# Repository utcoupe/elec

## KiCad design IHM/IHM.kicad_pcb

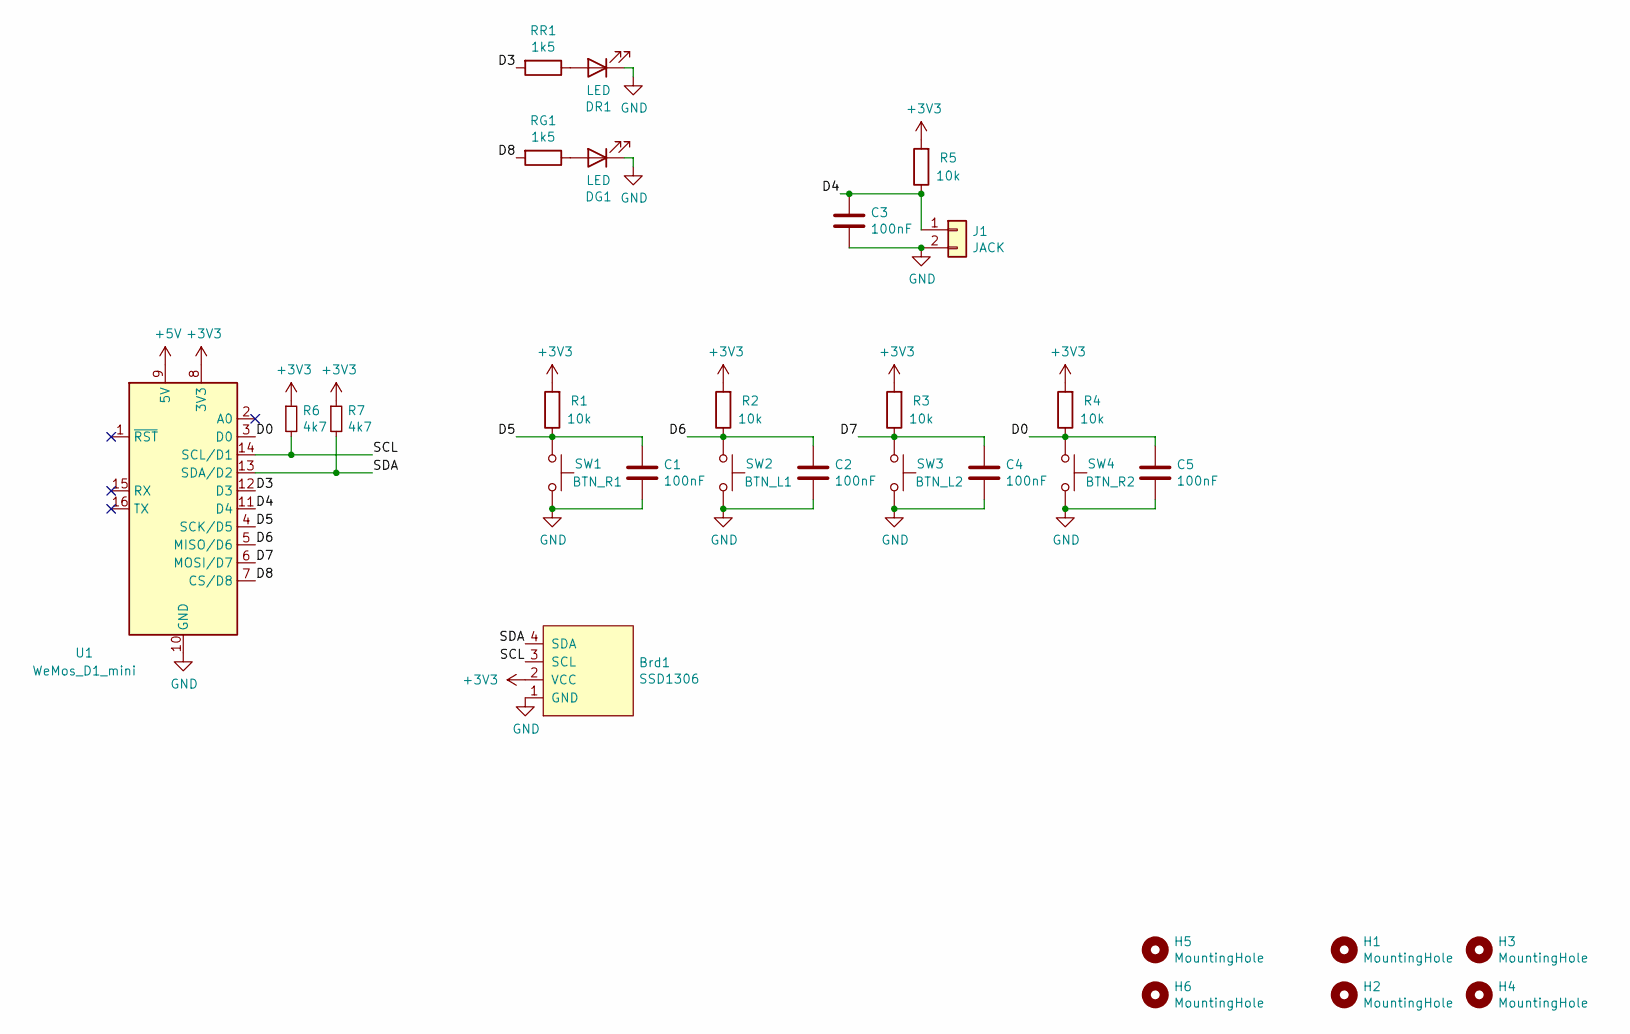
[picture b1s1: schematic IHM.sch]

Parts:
Brd1: SSD1306; 128x64OLED
C1, C2, C3, C4, C5: 100nF; C_0603_1608Metric; LCSC C14663
DG1: LED; LED_D3.0mm
DR1: LED; LED_D3.0mm
H1, H2, H3, H4: MountingHole; MountingHole_3.2mm_M3
H5, H6: MountingHole; MountingHole_2.2mm_M2
J1: JACK; PhoenixContact_MC_1,5_2-G-3.5_1x02_P3.50mm_Horizontal
R1, R2, R3, R4, R5: 10k; R_0603_1608Metric; LCSC C25804
R6, R7: 4k7; R_0603_1608Metric; LCSC C23162
RG1: 1k5; R_0603_1608Metric; LCSC C22843
RR1: 1k5; R_0603_1608Metric; LCSC C22843
SW1: BTN_R1; SW_PUSH_6mm_H4.3mm
SW2: BTN_L1; SW_PUSH_6mm_H4.3mm
SW3: BTN_L2; SW_PUSH_6mm_H4.3mm
SW4: BTN_R2; SW_PUSH_6mm_H4.3mm
U1: WeMos_D1_mini; WEMOS_D1_mini_light

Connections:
+3V3: Brd1.2 (VCC), R1.2, R2.2, R3.2, R4.2, R5.2, R6.1, R7.1, U1.8 (3V3)
+5V: U1.9 (5V)
/D0: C5.1, R4.1, SW4.1, U1.3 (D0)
/D3: RR1.2, U1.12 (D3)
/D4: C3.1, J1.1, R5.1, U1.11 (D4)
/D5: C1.1, R1.1, SW1.1, U1.4 (SCK/D5)
/D6: C2.1, R2.1, SW2.1, U1.5 (MISO/D6)
/D7: C4.1, R3.1, SW3.1, U1.6 (MOSI/D7)
/D8: RG1.2, U1.7 (CS/D8)
/SCL: Brd1.3 (SCL), R6.2, U1.14 (SCL/D1)
/SDA: Brd1.4 (SDA), R7.2, U1.13 (SDA/D2)
GND: Brd1.1 (GND), C1.2, C2.2, C3.2, C4.2, C5.2, DG1.1 (K), DR1.1 (K), J1.2, SW1.2, SW2.2, SW3.2, SW4.2, U1.10 (GND)
unnamed: DG1.2 (A), RG1.1
unnamed: DR1.2 (A), RR1.1

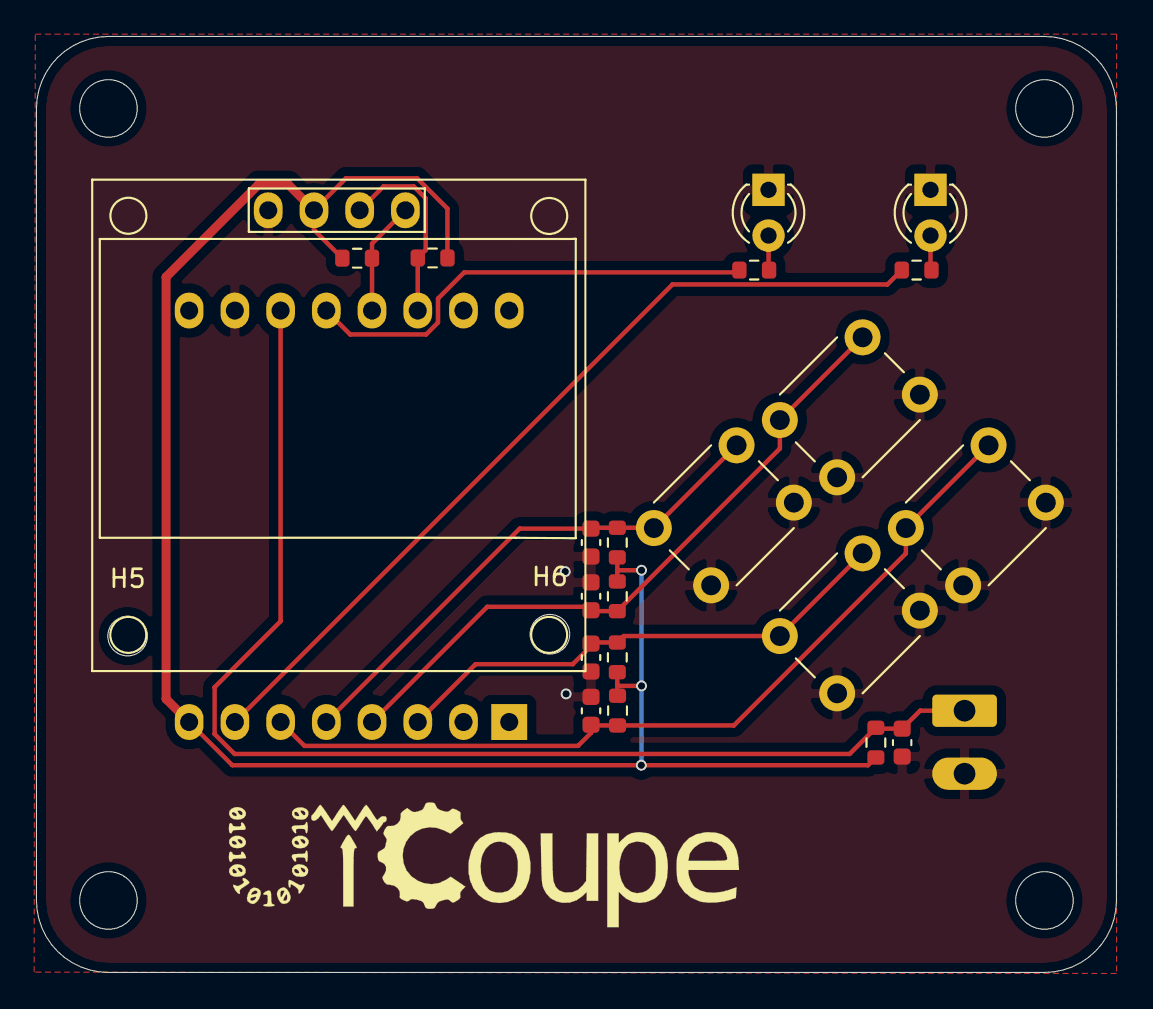
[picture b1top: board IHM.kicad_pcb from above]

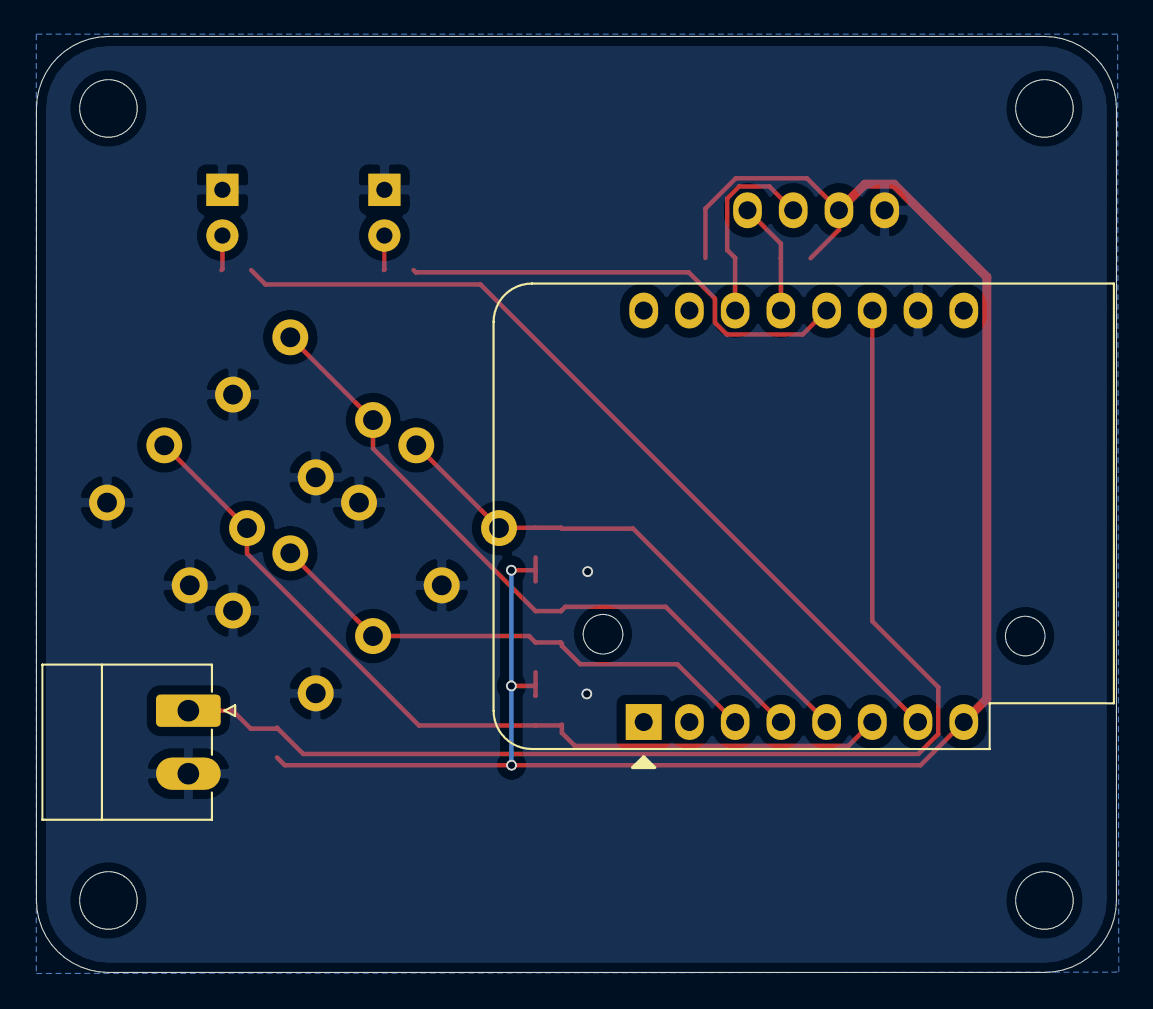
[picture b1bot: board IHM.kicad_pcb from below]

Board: 2 copper layers, 60.0 x 52.0 mm, 29 parts (2 on the bottom side), 13 nets.

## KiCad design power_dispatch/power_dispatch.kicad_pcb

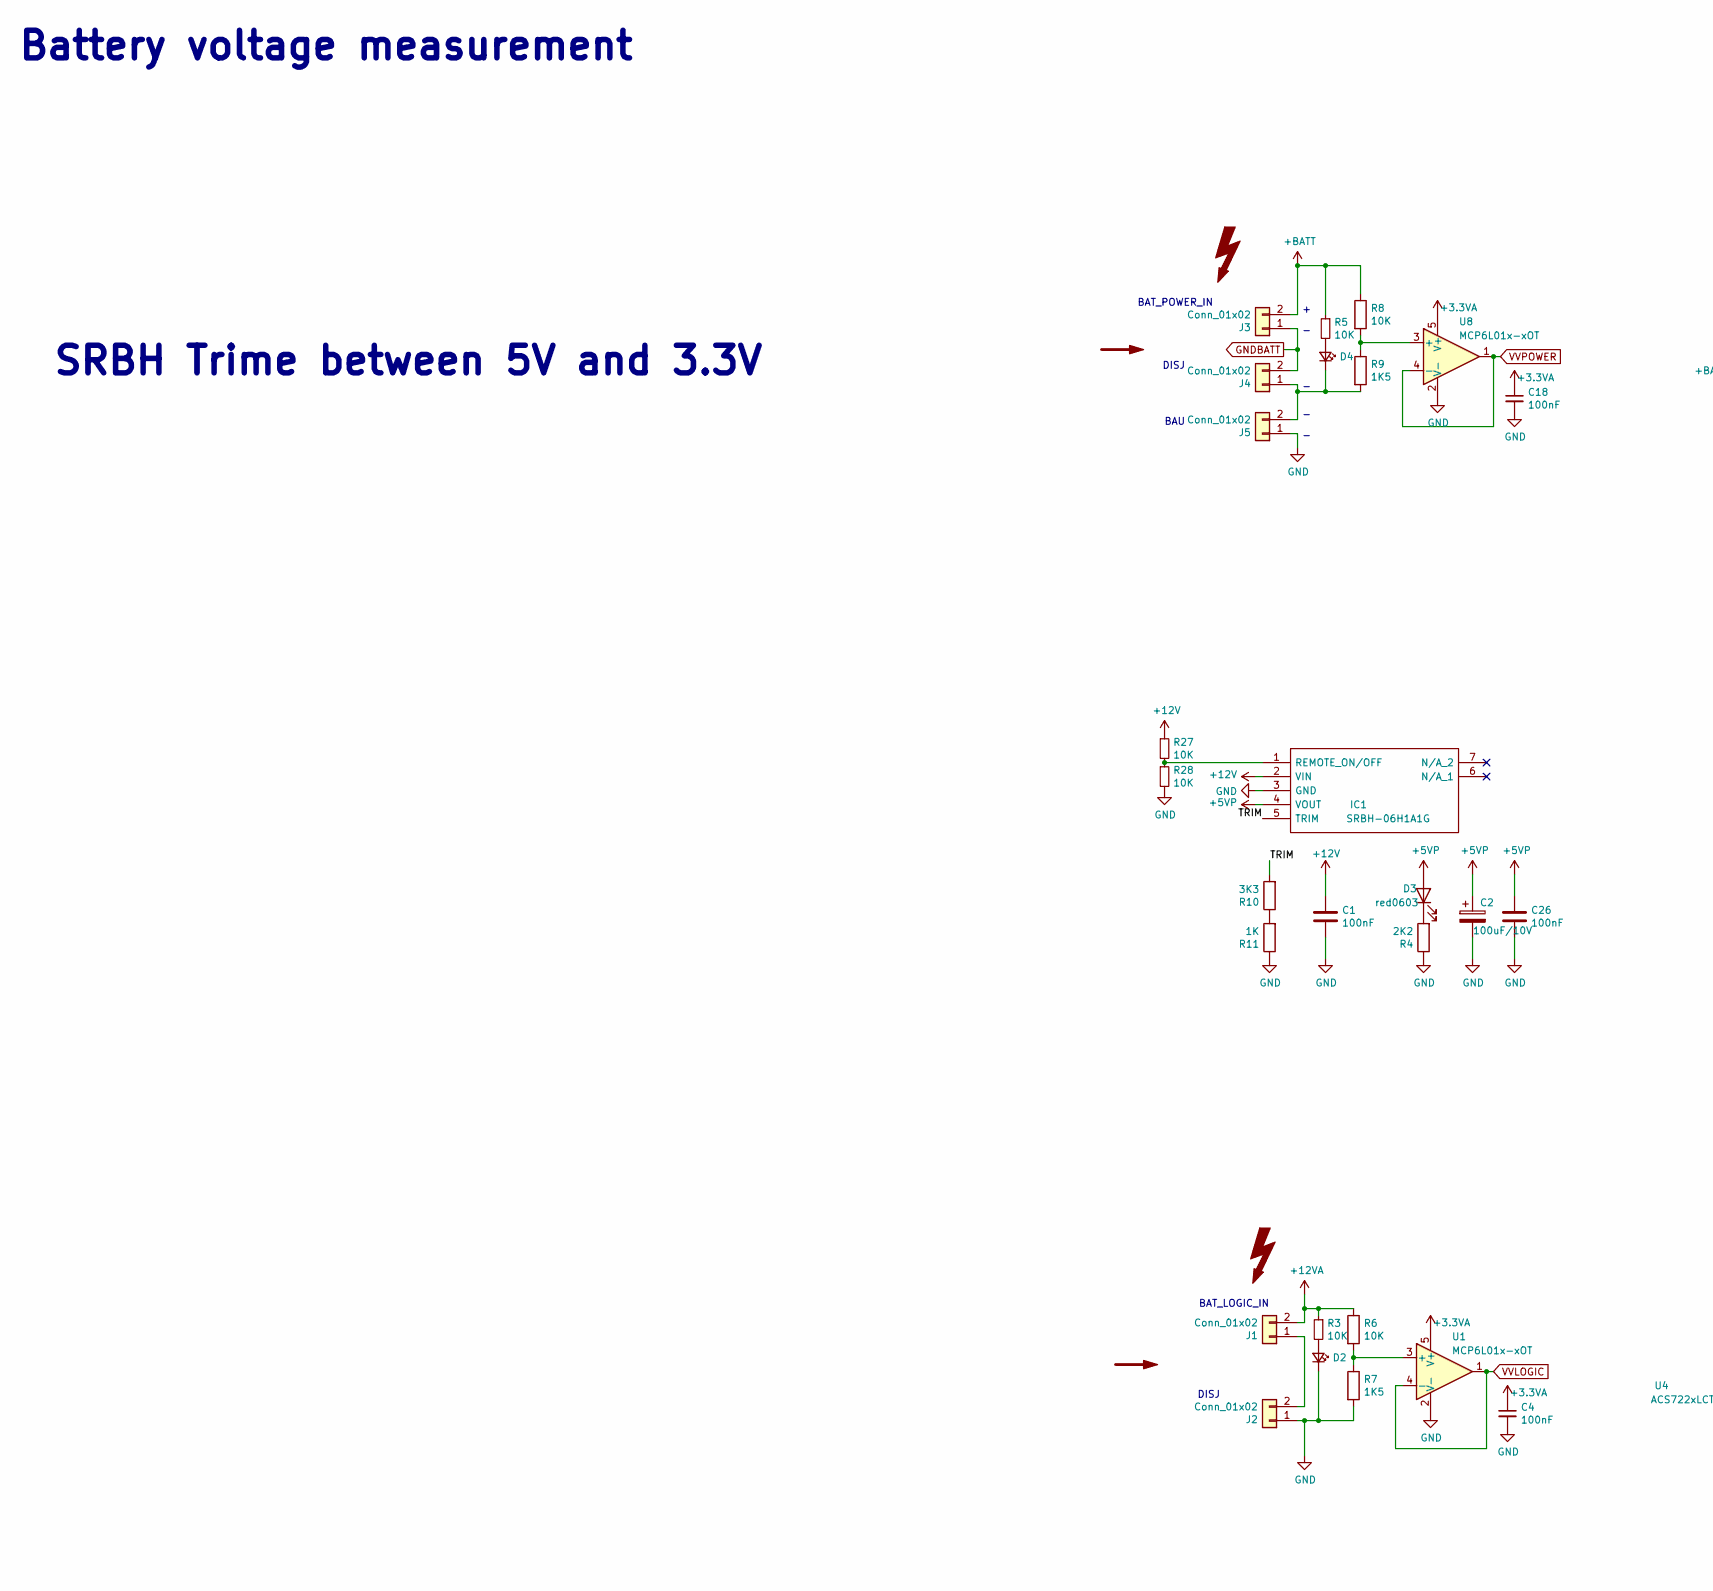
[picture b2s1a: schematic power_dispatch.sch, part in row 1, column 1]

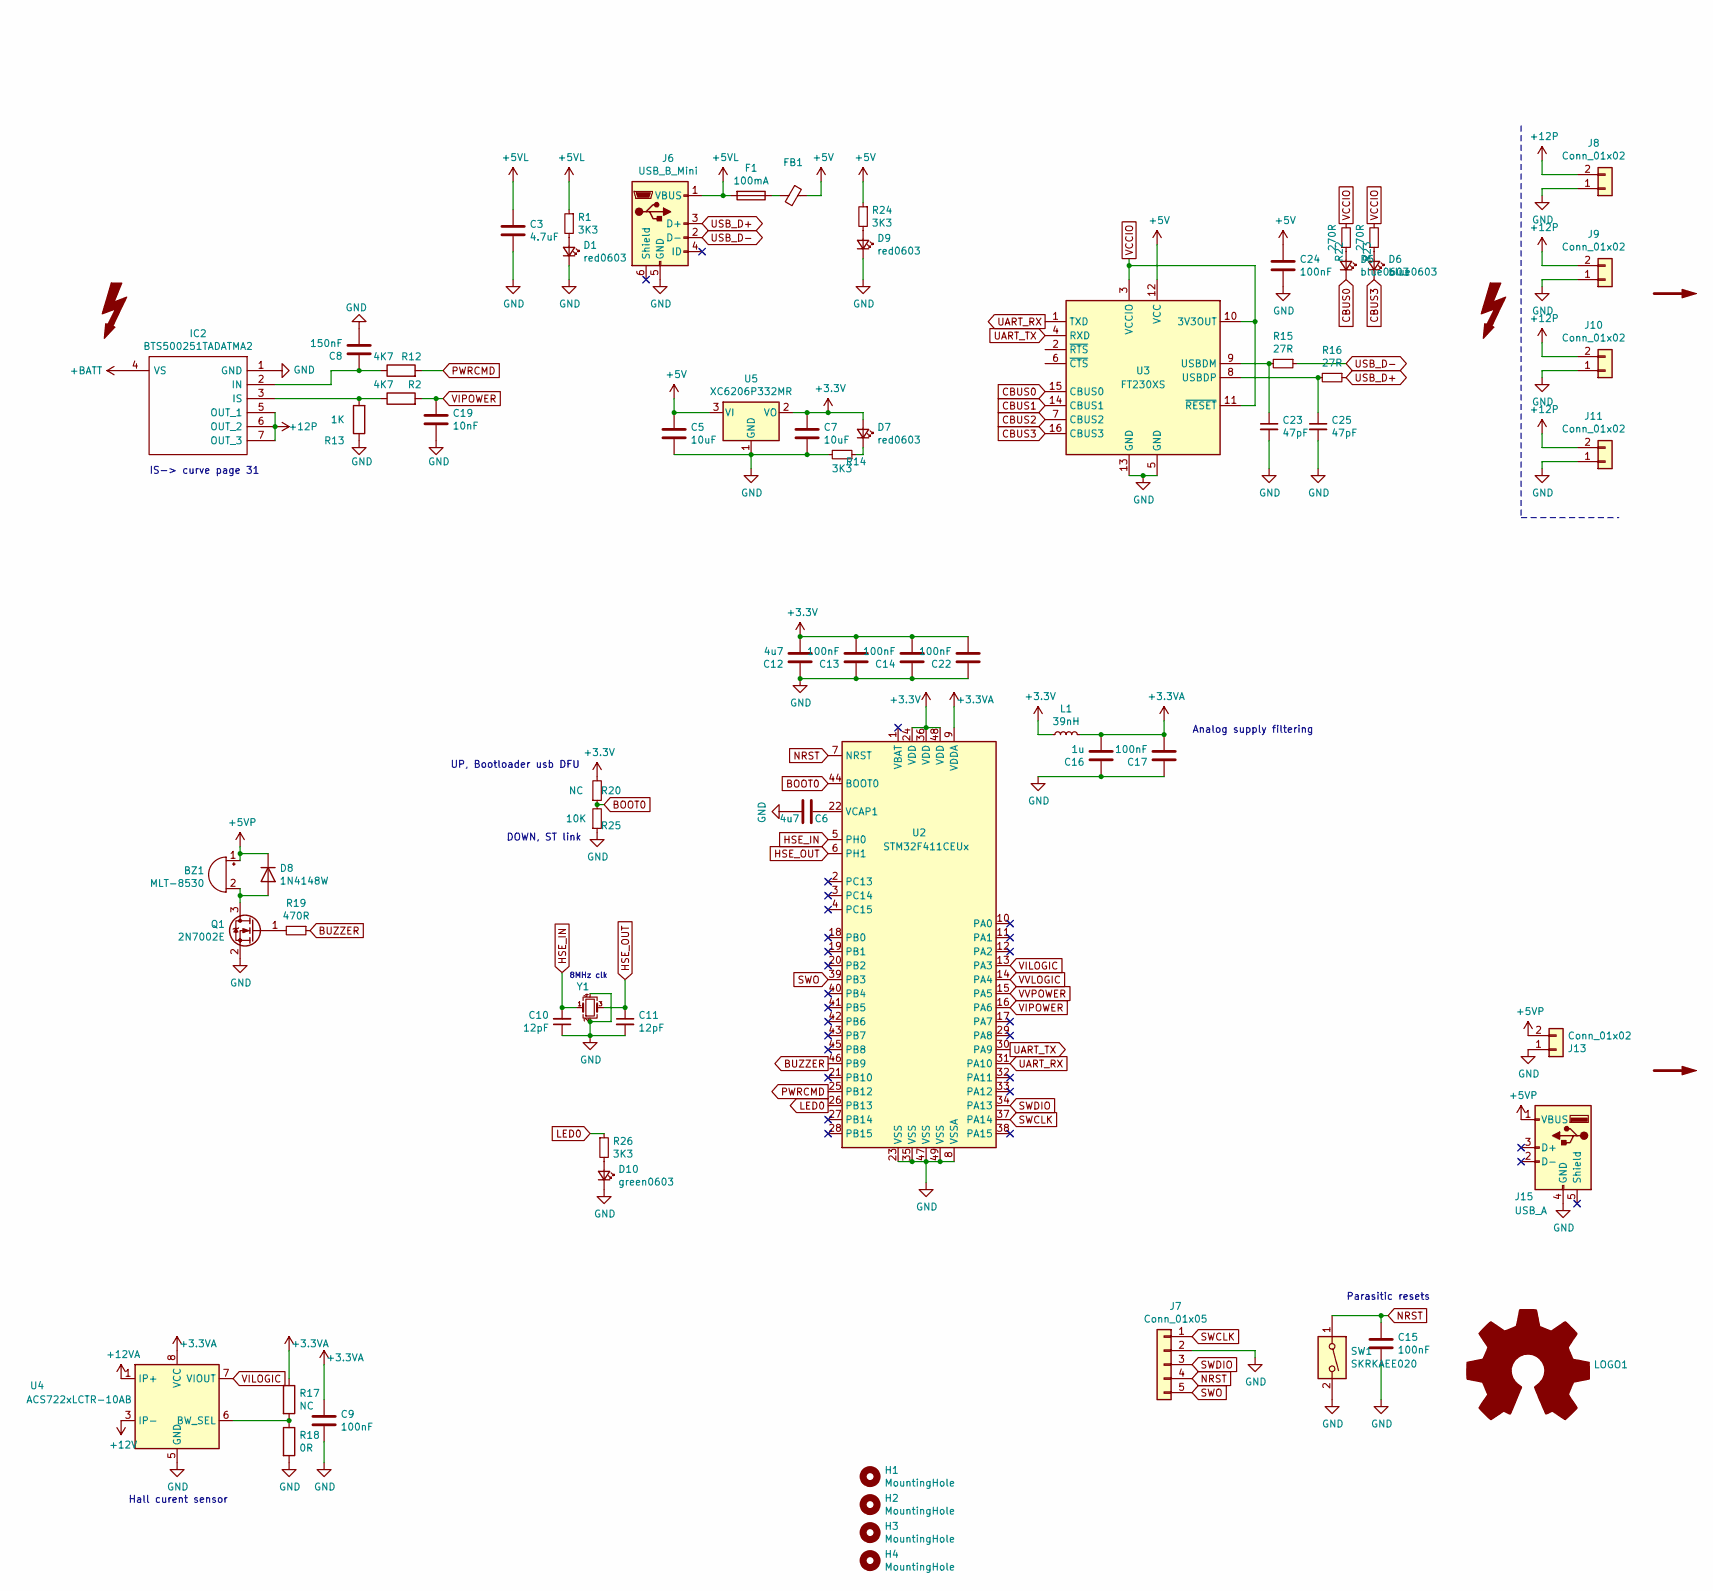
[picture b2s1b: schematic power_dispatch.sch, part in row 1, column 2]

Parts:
BZ1: MLT-8530; MagneticBuzzer_Kobitone_254-EMB84Q-RO
C1, C4, C9, C13, C14, C15, C17, C18, C22, C24, C26: 100nF; C_0603_1608Metric
C2: 100uF/10V; CP_Elec_5x5.4
C3: 4.7uF; C_0603_1608Metric
C5, C7: 10uF; C_0603_1608Metric
C6, C12: 4u7; C_0603_1608Metric
C8: 150nF; C_0603_1608Metric
C10, C11: 12pF; C_0603_1608Metric
C16: 1u; C_0603_1608Metric
C19: 10nF; C_0603_1608Metric
C23, C25: 47pF; C_0603_1608Metric
D1, D2, D3, D4, D7, D9: red0603; LED_0603_1608Metric
D5, D6: blue0603; LED_0603_1608Metric
D8: 1N4148W; D_SOD-123
D10: green0603; LED_0603_1608Metric
F1: 100mA; Fuse_0603_1608Metric
FB1: 100 @ 100MHz; L_0805_2012Metric
H1, H2, H3, H4: MountingHole; MountingHole_2.2mm_M2
IC1: SRBH-06H1A1G; SRBH06H1A1G; Manufacturer_Part_Number SRBH-06H1A1G; Mouser Part Number 784-SRBH-06H1A1G
IC2: BTS500251TADATMA2; IPB180N03S4L01; Manufacturer_Part_Number BTS500251TADATMA2; Mouser Part Number 726-BTS500251TADATM2
J1, J2, J3, J4, J5, J8, J9, J10, J11: Conn_01x02; PhoenixContact_MSTBA_2,5_2-G_1x02_P5.00mm_Horizontal
J6: USB_B_Mini; USB_Mini-B_Wuerth_65100516121_Horizontal
J7: Conn_01x05; PinHeader_1x05_P2.54mm_Vertical
J13: Conn_01x02; PhoenixContact_MC_1,5_2-G-3.5_1x02_P3.50mm_Horizontal
J15: USB_A; USB_A_Molex_67643_Horizontal
L1: 39nH; L_0603_1608Metric
LOGO1: Logo_Open_Hardware_Large; OSHW-Logo_7.5x8mm_SilkScreen
Q1: 2N7002E; SOT-23
R1, R10, R14, R24, R26: 3K3; R_0603_1608Metric
R2, R12: 4K7; R_0603_1608Metric
R3, R5, R6, R8, R25, R27, R28: 10K; R_0603_1608Metric
R4: 2K2; R_0603_1608Metric
R7, R9: 1K5; R_0603_1608Metric
R11, R13: 1K; R_0603_1608Metric
R15, R16: 27R; C_0603_1608Metric
R17, R20: NC; R_0603_1608Metric
R18: 0R; R_0603_1608Metric
R19: 470R; C_0603_1608Metric
R22, R23: 270R; R_0603_1608Metric
SW1: SKRKAEE020; SW_Push_SPST_NO_Alps_SKRK
U1, U8: MCP6L01x-xOT; SOT-23-5
U2: STM32F411CEUx; QFN-48-1EP_7x7mm_P0.5mm_EP5.6x5.6mm_ThermalVias
U3: FT230XS; SSOP-16_3.9x4.9mm_P0.635mm
U4: ACS722xLCTR-10AB; SOIC-8_3.9x4.9mm_P1.27mm
U5: XC6206P332MR; SOT-23
Y1: 1C208000BC0K 8MHz; Crystal_SMD_3225-4Pin_3.2x2.5mm

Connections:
+3.3VA: C4.1, C9.1, C16.2, C17.2, C18.1, L1.2, R17.1, U1.5 (V+), U2.9 (VDDA), U4.8 (VCC), U8.5 (V+)
+3V3: C7.1, C12.2, C13.2, C14.2, C22.2, D7.2 (A), L1.1, R20.2, U2.24 (VDD), U2.36 (VDD), U2.48 (VDD), U5.2 (VO)
+5V: C5.1, C24.1, FB1.1, R24.1, U3.12 (VCC), U5.3 (VI)
+5VL: C3.1, F1.2, J6.1 (VBUS), R1.1
+5VP: BZ1.1 (-), C2.1, C26.1, D3.2 (A), D8.1 (K), IC1.4 (VOUT), J13.2, J15.1 (VBUS)
+12P: IC2.5 (OUT_1), IC2.6 (OUT_2), IC2.7 (OUT_3), J8.2, J9.2, J10.2, J11.2
+12V: C1.1, IC1.2 (VIN), R27.1, U4.3 (IP-), U4.4 (IP-)
+12VA: J1.2, R3.1, R6.1, U4.1 (IP+), U4.2 (IP+)
+BATT: IC2.4 (VS), J3.2, R5.1, R8.1
/TRIM: IC1.5 (TRIM), R10.2
BOOT0: R20.1, R25.2, U2.44 (BOOT0)
BUZZER: R19.1, U2.46 (PB9)
CBUS0: D5.1 (K), U3.15 (CBUS0)
CBUS1: U3.14 (CBUS1)
CBUS2: U3.7 (CBUS2)
CBUS3: D6.1 (K), U3.16 (CBUS3)
GND: C1.2, C2.2, C3.2, C4.2, C5.2, C6.2, C7.2, C8.2, C9.2, C10.1, C11.2, C12.1, C13.1, C14.1, C15.2, C16.1, C17.1, C18.2, C19.2, C22.1, C23.2, C24.2, C25.2, C26.2, D1.1 (K), D2.1 (K), D9.1 (K), D10.1 (K), IC1.3 (GND), IC2.1 (GND), J2.1, J5.1, J6.5 (GND), J7.2, J8.1, J9.1, J10.1, J11.1, J13.1, J15.4 (GND), Q1.2 (S), R4.1, R7.2, R11.1, R13.1, R14.2, R18.2, R25.1, R28.2, SW1.2, U1.2 (V-), U2.8 (VSSA), U2.23 (VSS), U2.35 (VSS), U2.47 (VSS), U2.49 (VSS), U3.5 (GND), U3.13 (GND), U4.5 (GND), U5.1 (GND), U8.2 (V-), Y1.2, Y1.4
GNDBATT: J3.1, J4.2
HSE_IN: C10.2, U2.5 (PH0), Y1.1
HSE_OUT: C11.1, U2.6 (PH1), Y1.3
LED0: R26.1, U2.26 (PB13)
NRST: C15.1, J7.4, SW1.1, U2.7 (NRST)
unnamed: BZ1.2 (+), D8.2 (A), Q1.3 (D)
unnamed: C6.1, U2.22 (VCAP1)
unnamed: C8.1, IC2.2 (IN), R12.1
unnamed: C23.1, R15.2, U3.9 (USBDM)
unnamed: C25.1, R16.2, U3.8 (USBDP)
unnamed: D1.2 (A), R1.2
unnamed: D2.2 (A), R3.2
unnamed: D3.1 (K), R4.2
unnamed: D4.1 (K), J4.1, J5.2, R9.2
unnamed: D4.2 (A), R5.2
unnamed: D5.2 (A), R22.1
unnamed: D6.2 (A), R23.1
unnamed: D7.1 (K), R14.1
unnamed: D9.2 (A), R24.2
unnamed: D10.2 (A), R26.2
unnamed: F1.1, FB1.2
unnamed: IC1.1 (REMOTE_ON/OFF), R27.2, R28.1
unnamed: IC2.3 (IS), R2.1, R13.2
unnamed: J1.1, J2.2
unnamed: Q1.1 (G), R19.2
unnamed: R6.2, R7.1, U1.3 (+)
unnamed: R8.2, R9.1, U8.3 (+)
unnamed: R10.1, R11.2
unnamed: R17.2, R18.1, U4.6 (BW_SEL)
PWRCMD: R12.2, U2.25 (PB12)
SWCLK: J7.1, U2.37 (PA14)
SWDIO: J7.3, U2.34 (PA13)
SWO: J7.5, U2.39 (PB3)
UART_RX: U2.31 (PA10), U3.1 (TXD)
UART_TX: U2.30 (PA9), U3.4 (RXD)
USB_D+: J6.3 (D+), R16.1
USB_D-: J6.2 (D-), R15.1
VCCIO: R22.2, R23.2, U3.3 (VCCIO), U3.10 (3V3OUT), U3.11 (~RESET)
VILOGIC: U2.13 (PA3), U4.7 (VIOUT)
VIPOWER: C19.1, R2.2, U2.16 (PA6)
VVLOGIC: U1.1, U1.4 (-), U2.14 (PA4)
VVPOWER: U2.15 (PA5), U8.1, U8.4 (-)

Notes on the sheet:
BAT_POWER_IN
DISJ
BAU
UP, Bootloader usb DFU
DOWN, ST link
Parasitic resets
Analog supply filtering
8MHz clk
BAT_LOGIC_IN
Hall curent sensor
Battery voltage measurement
SRBH Trime between 5V and 3.3V
IS-> curve page 31

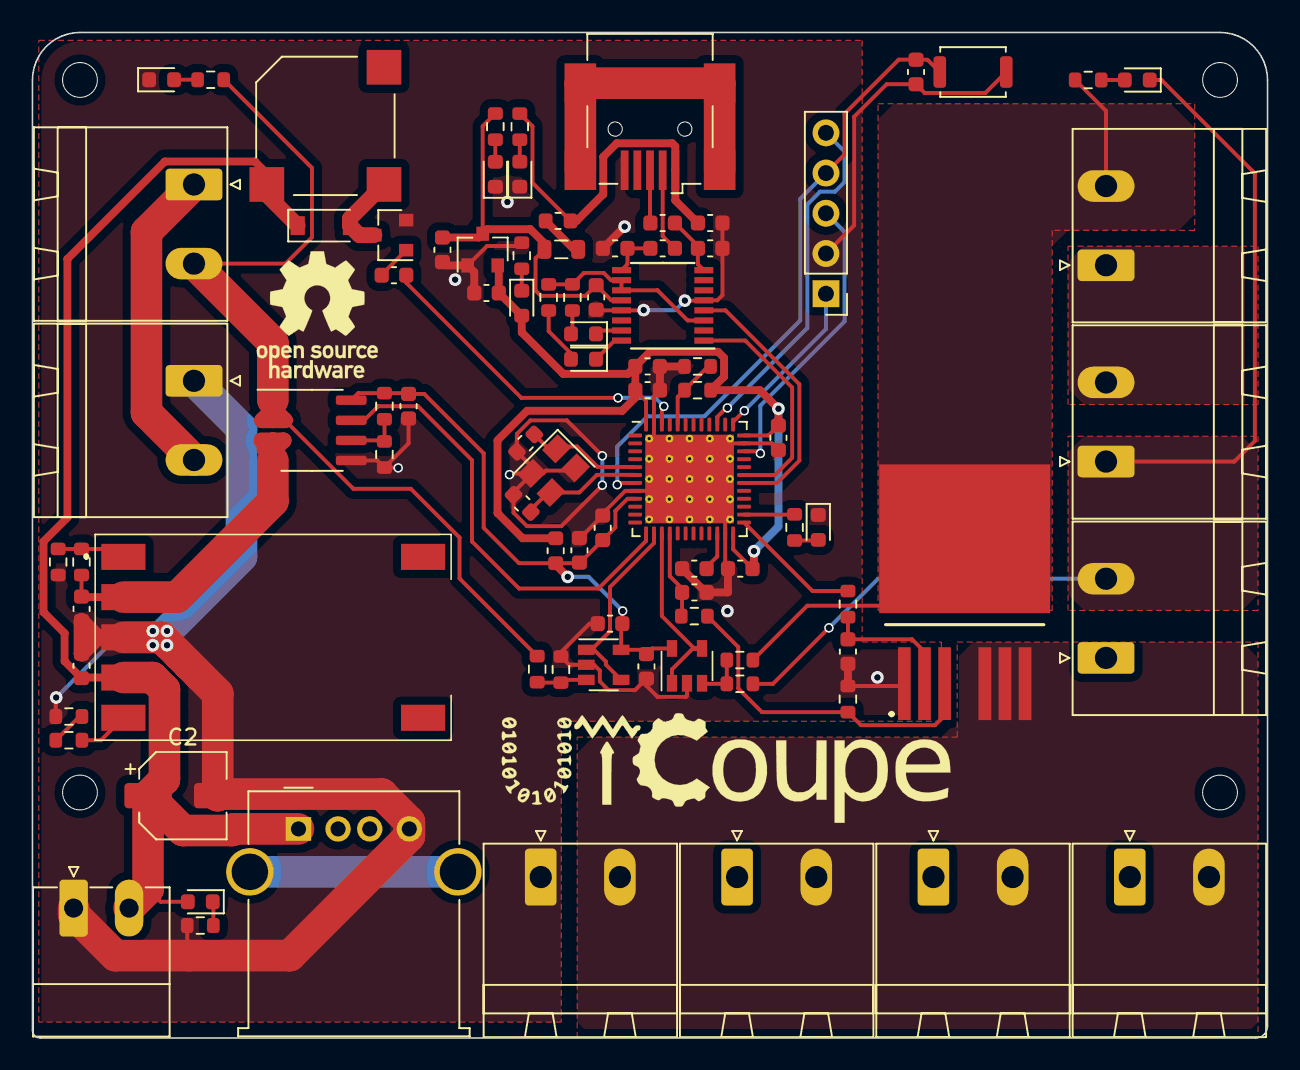
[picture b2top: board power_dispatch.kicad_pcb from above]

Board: 2 copper layers, 78.0 x 63.5 mm, 94 parts (0 on the bottom side), 57 nets.

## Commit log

2021-04-09 Add UTCoupe_lib
2021-04-09 Add power_dispatch
2021-04-09 Update pdf schematic
2021-04-09 Update lib paths
2021-04-09 Clean useless files
2021-05-15 Add SSD1306
2021-05-15 IHM project
2021-05-22 Schema + pcb de l'IHM
2021-05-28 Update UTCoupe lib
2021-05-28 Power dispatch V1.0
2021-05-28 Turbo brushless V1.0
2021-05-28 Add PCA9535PW,118
2021-05-28 Add actuators schematic
2021-05-29 Replace power symbols
2021-05-29 Add mounting holes
2021-05-29 Change push button logic
2021-05-29 Change led resistor values
2021-05-29 Rotate PCB
2021-05-30 Add jack connector
2021-05-30 Add I2C pull ups and capacitor on switches
2021-05-30 Change led res val
2021-05-30 Reroute
2021-05-30 Add 3D step of ssd1306
2021-05-31 Add oled step
2021-05-31 Update lib cache
2021-06-16 Update schematic
2021-06-16 Add LCSC references
